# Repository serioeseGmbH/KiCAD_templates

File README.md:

# Serious Templates
This repository provides KiCAD templates developed by employees of the [seriöse Gesellschaft ](https://serioese.gmbh).

## [ESP32-D2WD](http://esp32.net/#Hardware)
This is supposed to be a template for the new (28-09-2017) 2.4 GHz Wi-Fi with
16Mibit (2MiB) of integrated flash. The template sports the necessary bypass
capacitors, the RF filter and a SMD Antenna.

Most of the parts are found in [Seeedstudio OPL](https://www.seeedstudio.com/opl.html).

The files in this template depend on our
[ESP32 foorprints](https://github.com/serioeseGmbH/ESP32-kiCAD-Footprints) and
[Seeedstudio OPL](https://github.com/serioeseGmbH/OPL_Kicad_Library) repositories.
To reduce redundancy we omitted from including them as a submodule in this repository.
Please clone them yourself and include them in KiCAD.

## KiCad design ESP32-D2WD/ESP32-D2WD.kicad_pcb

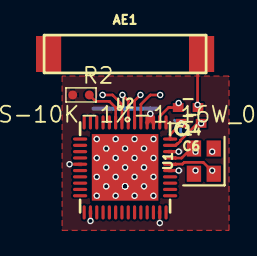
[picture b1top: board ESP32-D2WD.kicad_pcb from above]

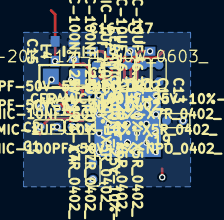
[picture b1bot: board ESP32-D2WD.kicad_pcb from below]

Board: 2 copper layers, 23 parts (17 on the bottom side), 13 nets.

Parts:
AE1: SMD_Built-in_Antenna_2.4GHz_9.5x2.1x1.0_; AN9520
C1, C2: CERAMIC-22PF-50V-5%-NPO_0402_; C0402
C3: CERAMIC-100PF-50V-5%-NPO_0402_; C0402
C4, C9, C10, C19: CERAMIC-100NF-25V-10%-X7R_0402_; C0402
C5: CERAMIC-10NF-50V-10%-X7R_0402_; C0402
C6: 3.3nF; C_0402
C11, C20: CERAMIC-1UF-10V-10%-X5R_0402_; C0402
C12, C13: CERAMIC-10UF-6.3V-20%-X5R_0402_; C0402
C14: 3.9pF; C_0402
C15: 2.4pF; C_0402
C16, C17: 270p; C_0402
L4: 2.7nH; L_0402
R1: SMD-RES-20K-1%-1_10W_0603_; R0603
R2: SMD-RES-10K-1%-1_16W_0402_; R0402
U1: 40MHz; Crystal_SMD_2016-4pin_2.0x1.6mm
U2: ESP32; QFN48_5x5_mm

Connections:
CHIP_PU: R2.2, U2.9
GND: C1.1, C2.2, C3.2, C4.2, C5.2, C9.2, C10.2, C11.2, C12.2, C13.2, C15.2, C19.2, C20.2, L4.2, U1.2, U1.4, U2.49
unnamed: AE1.1, C14.1, C15.1
unnamed: C1.2, U1.1, U2.44
unnamed: C2.1, U1.3, U2.45
unnamed: C5.1, C6.2, R1.2, U2.48
unnamed: C6.1, R1.1, U2.47
unnamed: C14.2, L4.1, U2.2
unnamed: C16.1, U2.5
unnamed: C16.2, U2.6
unnamed: C17.1, U2.7
unnamed: C17.2, U2.8
VCC: C3.1, C4.1, C9.1, C10.1, C11.1, C12.1, C13.1, C19.1, C20.1, R2.1, U2.1, U2.3, U2.4, U2.19, U2.26, U2.37, U2.43, U2.46

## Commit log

2017-09-14 added license and readme
2017-09-14 ignore backup files
2017-09-14 added kicad files
2017-09-14 added library path describing file
2017-09-14 added minimal meta directory to make it a kicad template
2017-09-25 refactored the template to be one directory deeper for kicad
2017-09-25 pulled updated lib
2017-09-25 added icon
2017-09-28 removed submodules from this repo to reduce redundancy; adapted readme
